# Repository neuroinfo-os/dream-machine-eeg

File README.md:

# Dream Machine
The Dream Machine, formerly known as *Traumschreiber*, is a lightweight, low-cost, mobile EEG device developed at the Neuroinforamtics group at Osnabrück University. This repository contains all affiliated projects and theses.

### This includes:
- BoardDesign: The Printed Circuit Board (PCB) design of the latest version and a collection of operation manuals of the most important hardware components
- Two App submodules, including the [standard version](https://github.com/denizmgun/EEG-DroidDesign) and an alternative version adapted for an [exemplary motor imagery task](https://github.com/denizmgun/DreamMachineThesisMod)
- The embedded system and Bluetooth Low Energy (BLE) implementation
- An implementation to perform an "Eyes Open, Eyes Closed" experiment with Labrecorder and lab streaming layer (LSL) as [submodule](https://github.com/mvidaldp/pylsl-keyboard-trigger)
- A collection of theses written with (older) versions of the Dream Machine   

*Please do not hesitate to contact us with any questions or ideas (Paria Samimi: psamimi@uni-osnabrueck.de, Laura Krieger: laura.krieger@uni-osnabrueck.de).*

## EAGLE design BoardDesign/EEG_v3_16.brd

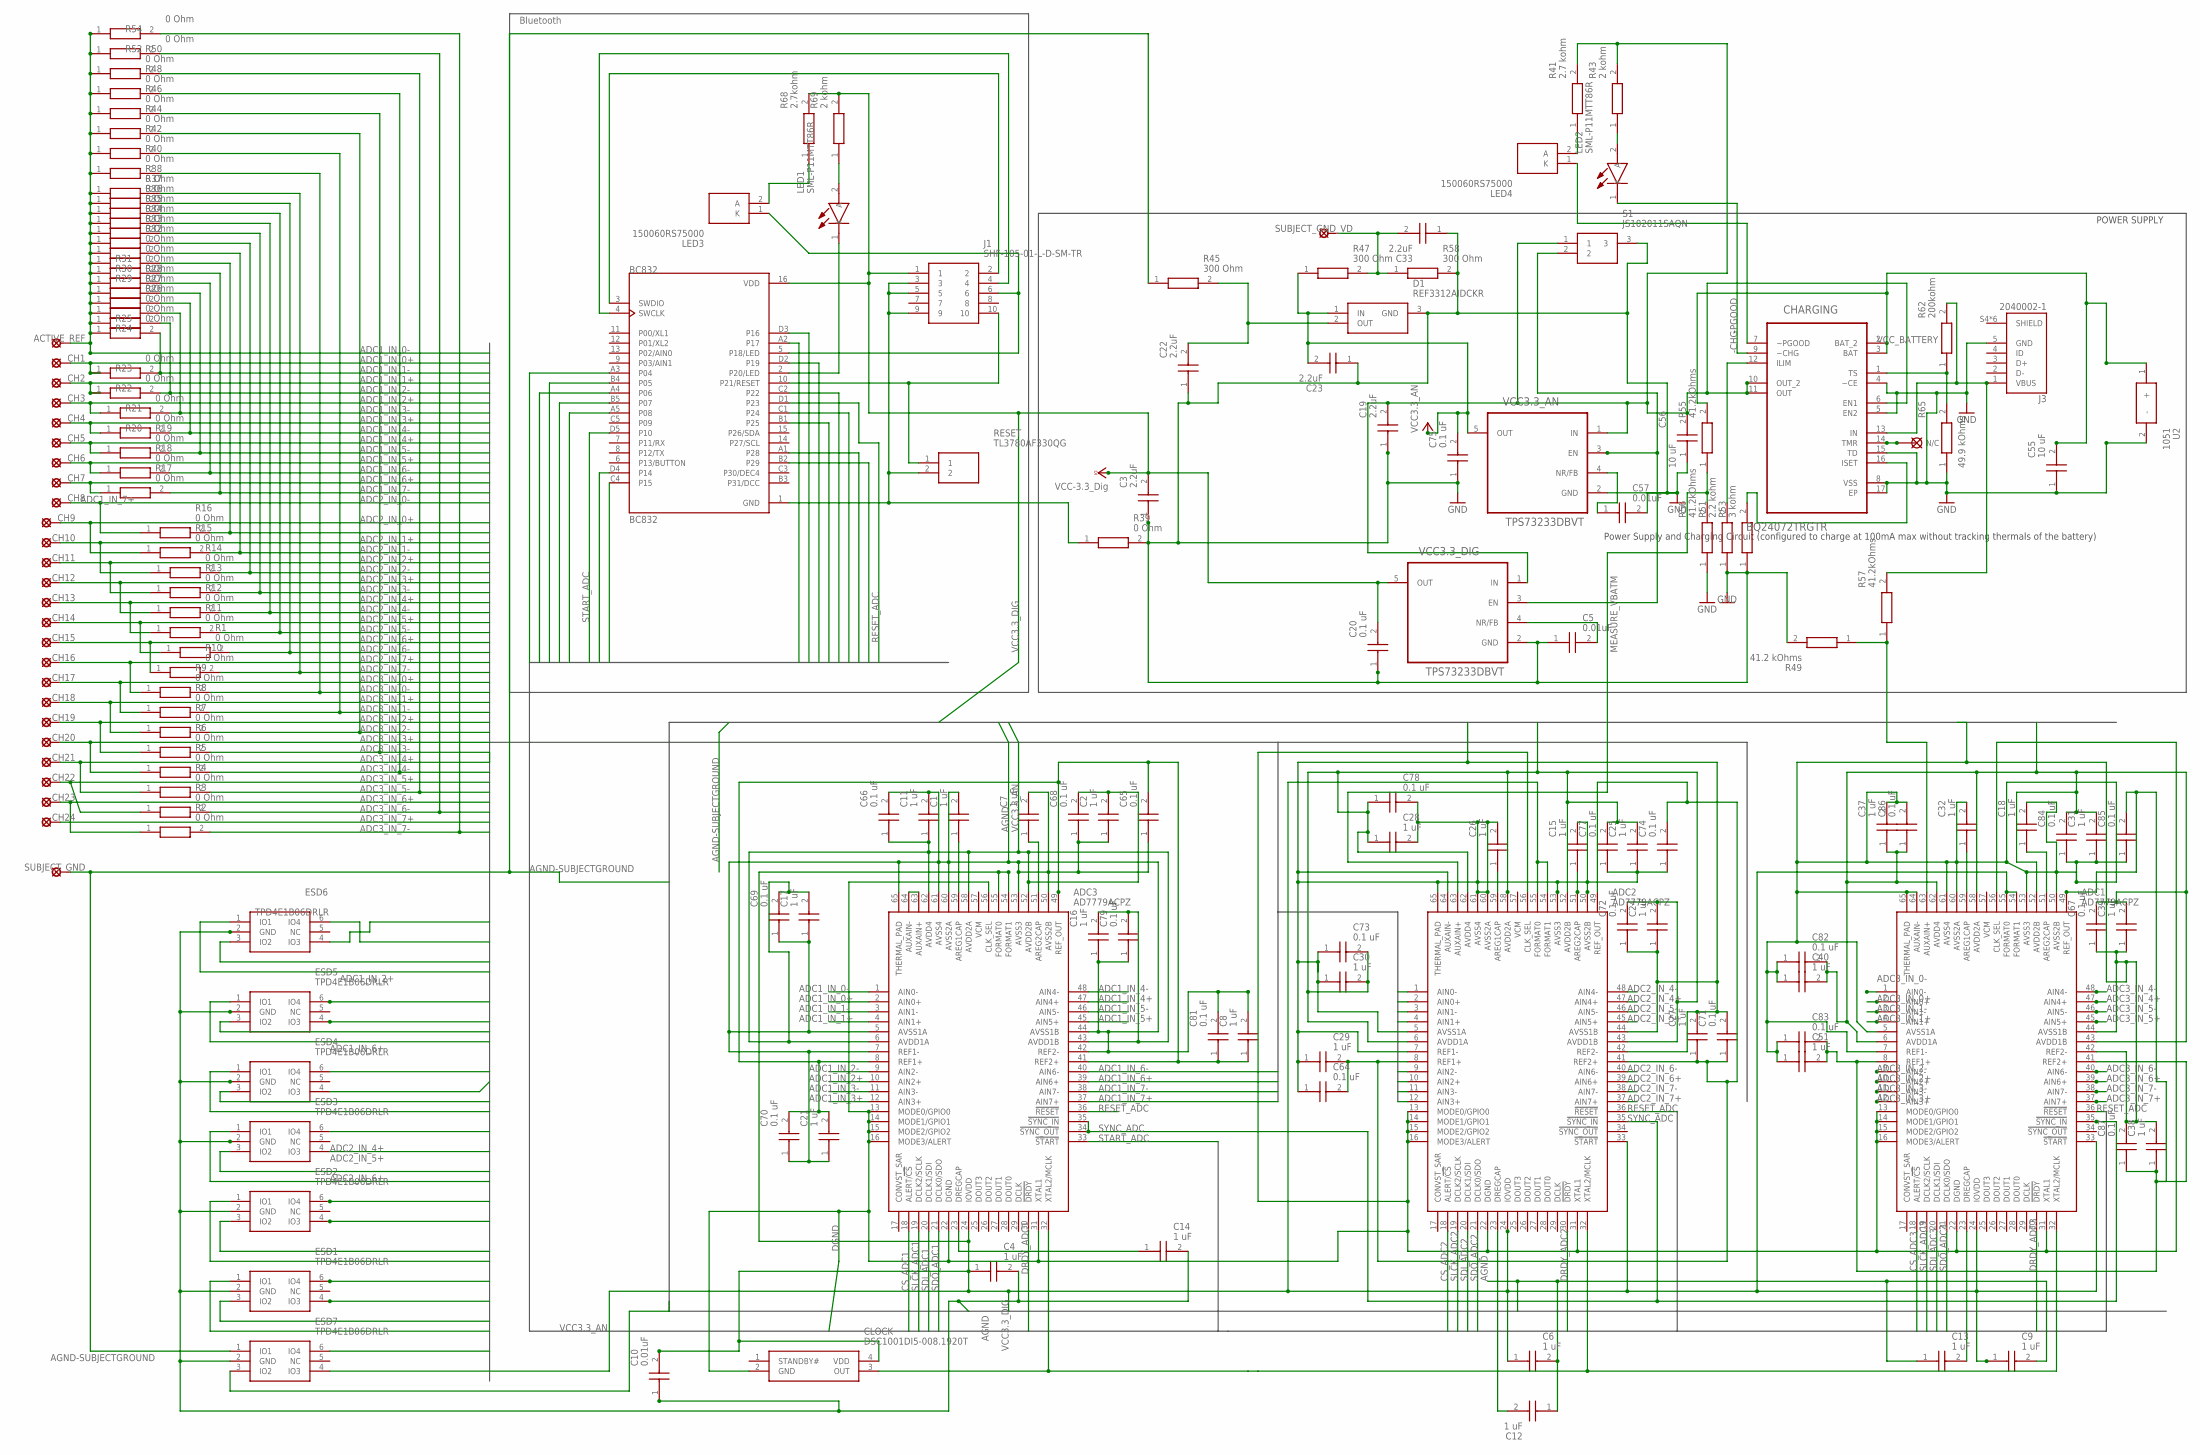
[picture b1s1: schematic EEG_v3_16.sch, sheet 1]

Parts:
ACTIVE_REF: SE11
ADC1, ADC2, ADC3: AD7779ACPZ; QFN50P900X900X80-65N
BC832: BC832; XCVR_BC832
C1, C2, C4, C6, C7, C8, C9, C11, C12, C13, C14, C15, C16, C17, C18, C21, C24, C25, C26, C27, C28, C29, C30, C31, C32, C37, C38, C39, C40, C51: 1 uF; CAPC1005X33N
C3, C19, C22, C23, C33: 2.2uF; CAPC0603X33N
C5, C10, C57: 0.01uF; CAPC0603X33N
C20, C64, C65, C66, C67, C68, C69, C70, C71, C72, C73, C74, C75, C77, C78, C79, C81, C82, C83, C84, C85, C86, C87: 0.1 uF; CAPC0603X33N
C55, C56: 10 uF; CAPC1608X100N
CH1, CH2, CH3, CH4, CH5, CH6, CH7, CH8, CH9, CH10, CH11, CH12, CH13, CH14, CH15, CH16, CH17, CH18, CH19, CH20, CH21, CH22, CH23, CH24: SE11
CHARGING: BQ24072TRGTR; QFN50P300X300X100-17N
CLOCK: DSC1001DI5-008.1920T; DSC1001DI50081920T
D1: REF3312AIDCKR; SOT65P210X110-3N
ESD1, ESD2, ESD3, ESD4, ESD5, ESD6, ESD7: TPD4E1B06DRLR; SOP50P160X60-6N
J1: SHF-105-01-L-D-SM-TR; SHF-105-01-X-D-SM-TR
J3: 2040002-1; TE_2040002-1
LED1, LED2: SML-P11MTT86R; LEDC1006X25N
LED3, LED4: 150060RS75000; LEDC1608X80N
R1, R2, R3, R4, R5, R6, R7, R8, R9, R10, R11, R12, R13, R14, R15, R16, R17, R18, R19, R20, R21, R22, R23, R24, R25, R26, R27, R28, R29, R30, R31, R32, R33, R34, R35, R36, R37, R38, R39, R40, R42, R44, R46, R48, R50, R52, R54: 0 Ohm; RESC1608X55N
R41: 2.7 kohm; RESC0603X26N
R43, R69: 2 kohm; RESC0603X26N
R45, R47, R58: 300 Ohm; RESC0603X26N
R49: 41.2 kOhms; RESC0603X28N
R51: 2.2 kohm; RESC0603X28N
R53: 3 kohm; RESC0603X26N
R55, R56, R57: 41.2kOhms; RESC0603X28N
R62: 200kohm; RESC0603X28N
R65: 49.9 kOhms; RESC0603X28N
R68: 2.7kohm; RESC0603X26N
RESET: TL3780AF330QG
S1: JS102011SAQN
SUBJECT_GND: SE11
SUBJECT_GND_VD: SE11
U2: 1051
VCC3.3_AN, VCC3.3_DIG: TPS73233DBVT; SOT95P280X145-5N

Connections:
-CHG: CHARGING.9 (~CHG), LED2.1 (K)
-PGOOD: CHARGING.7 (~PGOOD), LED4.1 (K)
ADC1_IN_0+: ADC3.2 (AIN0+), CH1.MP, ESD6.4 (IO3), R23.1
ADC1_IN_0-: ACTIVE_REF.MP, ADC3.1 (AIN0-), ESD6.6 (IO4), R24.1, R25.1, R26.1, R27.1, R28.1, R29.1, R30.1, R31.1, R32.1, R33.1, R34.1, R35.1, R36.1, R37.1, R38.1, R40.1, R42.1, R44.1, R46.1, R48.1, R50.1, R52.1, R54.1
ADC1_IN_1+: ADC3.4 (AIN1+), CH2.MP, ESD6.3 (IO2), R22.1
ADC1_IN_1-: ADC3.3 (AIN1-), R23.2, R24.2
ADC1_IN_2+: ADC3.10 (AIN2+), CH3.MP, ESD6.1 (IO1), R21.1
ADC1_IN_2-: ADC3.9 (AIN2-), R22.2, R25.2
ADC1_IN_3+: ADC3.12 (AIN3+), CH4.MP, ESD5.6 (IO4), R20.1
ADC1_IN_3-: ADC3.11 (AIN3-), R21.2, R26.2
ADC1_IN_4+: ADC3.47 (AIN4+), CH5.MP, ESD5.4 (IO3), R19.1
ADC1_IN_4-: ADC3.48 (AIN4-), R20.2, R27.2
ADC1_IN_5+: ADC3.45 (AIN5+), CH6.MP, ESD5.3 (IO2), R18.1
ADC1_IN_5-: ADC3.46 (AIN5-), R19.2, R28.2
ADC1_IN_6+: ADC3.39 (AIN6+), CH7.MP, ESD5.1 (IO1), R17.1
ADC1_IN_6-: ADC3.40 (AIN6-), R18.2, R29.2
ADC1_IN_7+: ADC3.37 (AIN7+), CH8.MP, ESD4.6 (IO4), R16.1
ADC1_IN_7-: ADC3.38 (AIN7-), R17.2, R30.2
ADC2_IN_0+: ADC2.2 (AIN0+), CH9.MP, ESD4.4 (IO3), R15.1
ADC2_IN_0-: ADC2.1 (AIN0-), R16.2, R31.2
ADC2_IN_1+: ADC2.4 (AIN1+), CH10.MP, ESD4.3 (IO2), R14.1
ADC2_IN_1-: ADC2.3 (AIN1-), R15.2, R32.2
ADC2_IN_2+: ADC2.10 (AIN2+), CH11.MP, ESD4.1 (IO1), R13.1
ADC2_IN_2-: ADC2.9 (AIN2-), R14.2, R33.2
ADC2_IN_3+: ADC2.12 (AIN3+), CH12.MP, ESD3.6 (IO4), R12.1
ADC2_IN_3-: ADC2.11 (AIN3-), R13.2, R34.2
ADC2_IN_4+: ADC2.47 (AIN4+), CH13.MP, ESD3.4 (IO3), R11.1
ADC2_IN_4-: ADC2.48 (AIN4-), R12.2, R35.2
ADC2_IN_5+: ADC2.45 (AIN5+), CH14.MP, ESD3.3 (IO2), R1.1
ADC2_IN_5-: ADC2.46 (AIN5-), R11.2, R36.2
ADC2_IN_6+: ADC2.39 (AIN6+), CH15.MP, ESD3.1 (IO1), R10.1
ADC2_IN_6-: ADC2.40 (AIN6-), R1.2, R37.2
ADC2_IN_7+: ADC2.37 (AIN7+), CH16.MP, ESD2.6 (IO4), R9.1
ADC2_IN_7-: ADC2.38 (AIN7-), R10.2, R38.2
ADC3_IN_0+: ADC1.2 (AIN0+), CH17.MP, ESD2.4 (IO3), R8.1
ADC3_IN_0-: ADC1.1 (AIN0-), R9.2, R40.2
ADC3_IN_1+: ADC1.4 (AIN1+), CH18.MP, ESD2.3 (IO2), R7.1
ADC3_IN_1-: ADC1.3 (AIN1-), R8.2, R42.2
ADC3_IN_2+: ADC1.10 (AIN2+), CH19.MP, ESD2.1 (IO1), R6.1
ADC3_IN_2-: ADC1.9 (AIN2-), R7.2, R44.2
ADC3_IN_3+: ADC1.12 (AIN3+), CH20.MP, ESD1.6 (IO4), R5.1
ADC3_IN_3-: ADC1.11 (AIN3-), R6.2, R46.2
ADC3_IN_4+: ADC1.47 (AIN4+), CH21.MP, ESD1.4 (IO3), R4.1
ADC3_IN_4-: ADC1.48 (AIN4-), R5.2, R48.2
ADC3_IN_5+: ADC1.45 (AIN5+), CH22.MP, ESD1.3 (IO2), R3.1
ADC3_IN_5-: ADC1.46 (AIN5-), R4.2, R50.2
ADC3_IN_6+: ADC1.39 (AIN6+), CH23.MP, ESD1.1 (IO1), R2.1
ADC3_IN_6-: ADC1.40 (AIN6-), R3.2, R52.2
ADC3_IN_7+: ADC1.37 (AIN7+), CH24.MP, ESD7.6 (IO4)
ADC3_IN_7-: ADC1.38 (AIN7-), R2.2, R54.2
AGND: ADC1.5 (AVSS1A), ADC1.7 (REF1-), ADC1.42 (REF2-), ADC1.44 (AVSS1B), ADC1.50 (AVSS2B), ADC1.53 (AVSS3), ADC1.60 (AVSS2A), ADC1.61 (AVSS4), ADC1.64 (AUXAIN-), ADC1.65 (THERMAL_PAD), ADC2.5 (AVSS1A), ADC2.7 (REF1-), ADC2.42 (REF2-), ADC2.44 (AVSS1B), ADC2.50 (AVSS2B), ADC2.53 (AVSS3), ADC2.60 (AVSS2A), ADC2.61 (AVSS4), ADC2.64 (AUXAIN-), ADC2.65 (THERMAL_PAD), ADC3.5 (AVSS1A), ADC3.7 (REF1-), ADC3.42 (REF2-), ADC3.44 (AVSS1B), ADC3.50 (AVSS2B), ADC3.53 (AVSS3), ADC3.60 (AVSS2A), ADC3.61 (AVSS4), ADC3.65 (THERMAL_PAD), C1.2, C2.1, C3.1, C4.2, C5.1, C6.2, C7.2, C8.2, C9.2, C10.1, C11.2, C12.1, C13.1, C14.2, C15.2, C16.1, C17.1, C18.2, C19.1, C20.1, C21.1, C22.1, C23.1, C24.1, C25.1, C26.2, C27.2, C28.2, C29.1, C30.1, C31.1, C32.2, C33.1, C37.2, C38.2, C39.1, C40.1, C51.1, C55.1, C56.1, C57.2, C64.1, C65.1, C66.2, C67.1, C68.1, C69.1, C70.1, C71.2, C72.1, C73.1, C74.1, C75.1, C77.1, C78.2, C79.1, C81.2, C82.1, C83.1, C84.1, C85.1, C86.2, C87.2, CHARGING.4 (~CE), CHARGING.5 (EN2), CHARGING.8 (VSS), CHARGING.15 (TD), CHARGING.17 (EP), D1.3 (GND), ESD1.2 (GND), ESD2.2 (GND), ESD3.2 (GND), ESD4.2 (GND), ESD5.2 (GND), ESD6.2 (GND), ESD7.2 (GND), J3.5 (GND), R39.2, R49.2, R51.1, R53.1, R56.1, R58.2, R65.1, S1.3, U2.2 (-), VCC3.3_AN.2 (GND), VCC3.3_DIG.2 (GND)
AGND-SUBJECTGROUND: ESD7.1 (IO1), R45.1, SUBJECT_GND.MP
CS_ADC1: ADC3.18 (ALERT/!CS), BC832.A4 (P06)
CS_ADC2: ADC2.18 (ALERT/!CS), BC832.A5 (P08)
CS_ADC3: ADC1.18 (ALERT/!CS), BC832.C1 (P24)
DGND: ADC1.13 (MODE0/GPIO0), ADC1.14 (MODE1/GPIO1), ADC1.15 (MODE2/GPIO2), ADC1.16 (MODE3/ALERT), ADC1.22 (DGND), ADC1.31 (XTAL1), ADC1.56 (CLK_SEL), ADC2.13 (MODE0/GPIO0), ADC2.14 (MODE1/GPIO1), ADC2.15 (MODE2/GPIO2), ADC2.16 (MODE3/ALERT), ADC2.22 (DGND), ADC2.31 (XTAL1), ADC2.56 (CLK_SEL), ADC3.13 (MODE0/GPIO0), ADC3.14 (MODE1/GPIO1), ADC3.15 (MODE2/GPIO2), ADC3.16 (MODE3/ALERT), ADC3.22 (DGND), ADC3.31 (XTAL1), ADC3.56 (CLK_SEL), BC832.1 (GND), CLOCK.2 (GND), J1.3, J1.5, J1.9, R39.1, RESET.2
DRDY_ADC1: ADC3.30 (!DRDY), BC832.A2 (P17)
DRDY_ADC2: ADC2.30 (!DRDY), BC832.D4 (P14)
DRDY_ADC3: ADC1.30 (!DRDY), BC832.B1 (P25)
MEASURE_VBATM: ADC2.63 (AUXAIN+), R55.1, R56.2
MEASURE_VUSB: ADC1.63 (AUXAIN+), R49.1, R57.1
unnamed: ADC3.59 (AREG1CAP), C1.1
unnamed: ADC2.23 (DREGCAP), C12.2
unnamed: C22.2, D1.2 (OUT), R45.2
unnamed: C5.2, VCC3.3_DIG.4 (NR/FB)
unnamed: BC832.2 (P20/LED), LED1.1 (K)
unnamed: ADC3.63 (AUXAIN+), ADC3.64 (AUXAIN-)
unnamed: ADC3.51 (AREG2CAP), C7.1
unnamed: LED3.2 (A), R68.1
unnamed: LED1.2 (A), R69.1
unnamed: LED4.2 (A), R41.1
unnamed: ADC2.51 (AREG2CAP), C15.1
unnamed: ADC3.23 (DREGCAP), C14.1
unnamed: ADC1.23 (DREGCAP), C13.2
unnamed: LED2.2 (A), R43.1
unnamed: C57.1, VCC3.3_AN.4 (NR/FB)
unnamed: ADC1.59 (AREG1CAP), C32.1
unnamed: ADC2.59 (AREG1CAP), C26.1
unnamed: ADC1.51 (AREG2CAP), C18.1
unnamed: CHARGING.1 (TS), R62.1, R65.2
unnamed: CHARGING.16 (ISET), R53.2
unnamed: CHARGING.12 (ILIM), R51.2
P18/LED: BC832.5 (P18/LED), J1.6, LED3.1 (K)
POWERUP: S1.2, VCC3.3_AN.3 (EN), VCC3.3_DIG.3 (EN)
REF_ADC1: ADC3.8 (REF1+), ADC3.41 (REF2+), ADC3.49 (REF_OUT), C8.1, C21.2, C65.2, C70.2, C81.1
REF_ADC2: ADC2.8 (REF1+), ADC2.41 (REF2+), ADC2.49 (REF_OUT), C27.1, C29.2, C64.2, C71.1, C74.2
REF_ADC3: ADC1.8 (REF1+), ADC1.41 (REF2+), ADC1.49 (REF_OUT), C38.1, C51.2, C83.2, C85.2, C87.1
RESET: BC832.10 (P21/RESET), J1.10, RESET.1
RESET_ADC: ADC1.36 (!RESET), ADC2.36 (!RESET), ADC3.36 (!RESET), BC832.D1 (P23)
SDCLK: BC832.4 (SWCLK), J1.4
SDIO: BC832.3 (SWDIO), J1.2
SDI_ADC1: ADC3.20 (DCLK1/SDI), BC832.C4 (P15)
SDI_ADC2: ADC2.20 (DCLK1/SDI), BC832.B5 (P07)
SDI_ADC3: ADC1.20 (DCLK1/SDI), BC832.A1 (P28)
SDO_ADC1: ADC3.21 (DCLK0/SDO), BC832.D3 (P16)
SDO_ADC2: ADC2.21 (DCLK0/SDO), BC832.B4 (P05)
SDO_ADC3: ADC1.21 (DCLK0/SDO), BC832.B2 (P29)
SHIELD: J3.S4 (SHIELD), J3.S5 (SHIELD), J3.SH1 (SHIELD), J3.SH2 (SHIELD), J3.SH3 (SHIELD), J3.SH4 (SHIELD)
SLCK_ADC1: ADC3.19 (DCLK2/SCLK), BC832.A3 (P04)
SLCK_ADC2: ADC2.19 (DCLK2/SCLK), BC832.D2 (P19)
SLCK_ADC3: ADC1.19 (DCLK2/SCLK), BC832.C2 (P22)
START_ADC: ADC3.33 (!START), BC832.D5 (P10)
SYNC_ADC: ADC1.35 (!SYNC_IN), ADC2.35 (!SYNC_IN), ADC3.34 (!SYNC_OUT), ADC3.35 (!SYNC_IN)
USB_5VOLT+: CHARGING.13 (IN), J3.1 (VBUS), R57.2, R62.2
VCC3.3_AN: ADC1.6 (AVDD1A), ADC1.43 (AVDD1B), ADC1.52 (AVDD2B), ADC1.58 (AVDD2A), ADC1.62 (AVDD4), ADC2.6 (AVDD1A), ADC2.43 (AVDD1B), ADC2.52 (AVDD2B), ADC2.58 (AVDD2A), ADC2.62 (AVDD4), ADC3.6 (AVDD1A), ADC3.43 (AVDD1B), ADC3.52 (AVDD2B), ADC3.58 (AVDD2A), ADC3.62 (AVDD4), C2.2, C11.1, C16.2, C17.2, C23.2, C24.2, C25.2, C28.1, C30.2, C31.2, C37.1, C39.2, C40.2, C66.1, C67.2, C68.2, C69.2, C72.2, C73.2, C75.2, C77.2, C78.1, C79.2, C82.2, C84.2, C86.1, D1.1 (IN), ESD7.3 (IO2), R47.1, VCC3.3_AN.5 (OUT)
VCC3.3_DIG: ADC1.24 (IOVDD), ADC1.33 (!START), ADC1.54 (FORMAT1), ADC1.55 (FORMAT0), ADC2.24 (IOVDD), ADC2.33 (!START), ADC2.54 (FORMAT1), ADC2.55 (FORMAT0), ADC3.24 (IOVDD), ADC3.54 (FORMAT1), ADC3.55 (FORMAT0), BC832.16 (VDD), C3.2, C4.1, C6.1, C9.1, C10.2, C20.2, CLOCK.4 (VDD), ESD7.4 (IO3), J1.1, R68.2, R69.2, VCC3.3_DIG.5 (OUT)
VCC_BATTERY: C55.2, CHARGING.2 (BAT_2), CHARGING.3 (BAT), R55.2, U2.1 (+)
VIRTUAL_GND_PASSIVE: C33.2, R47.2, R58.1, SUBJECT_GND_VD.MP
V_OUT_CHARGER: C19.2, C56.2, CHARGING.6 (EN1), CHARGING.10 (OUT_2), CHARGING.11 (OUT), R41.2, R43.2, S1.1, VCC3.3_AN.1 (IN), VCC3.3_DIG.1 (IN)
XTAL_OUT: ADC1.32 (XTAL2/MCLK), ADC2.32 (XTAL2/MCLK), ADC3.32 (XTAL2/MCLK), CLOCK.3 (OUT)

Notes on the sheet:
Power Supply and Charging Circuit (configured to charge at 100mA max without tracking thermals of the battery)
POWER SUPPLY
Bluetooth

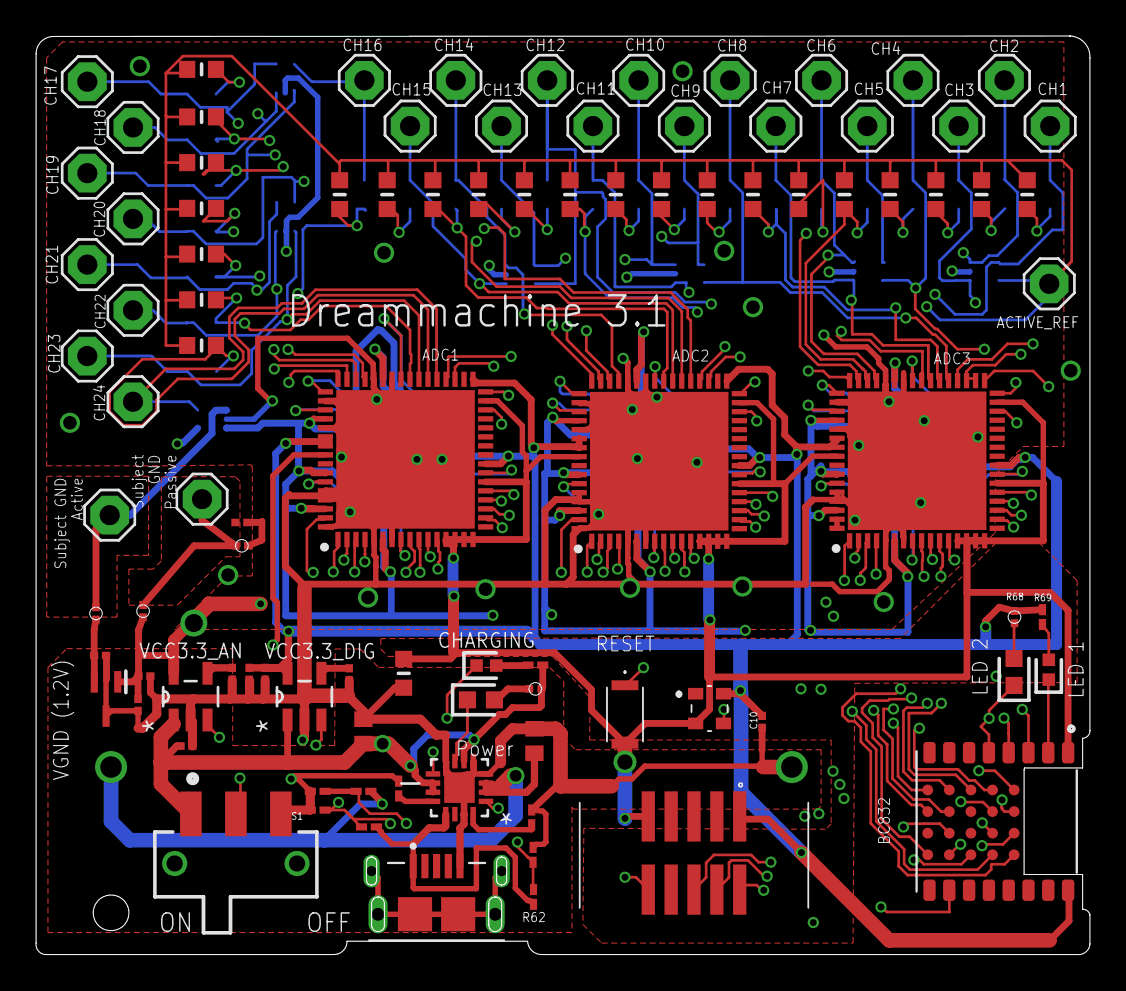
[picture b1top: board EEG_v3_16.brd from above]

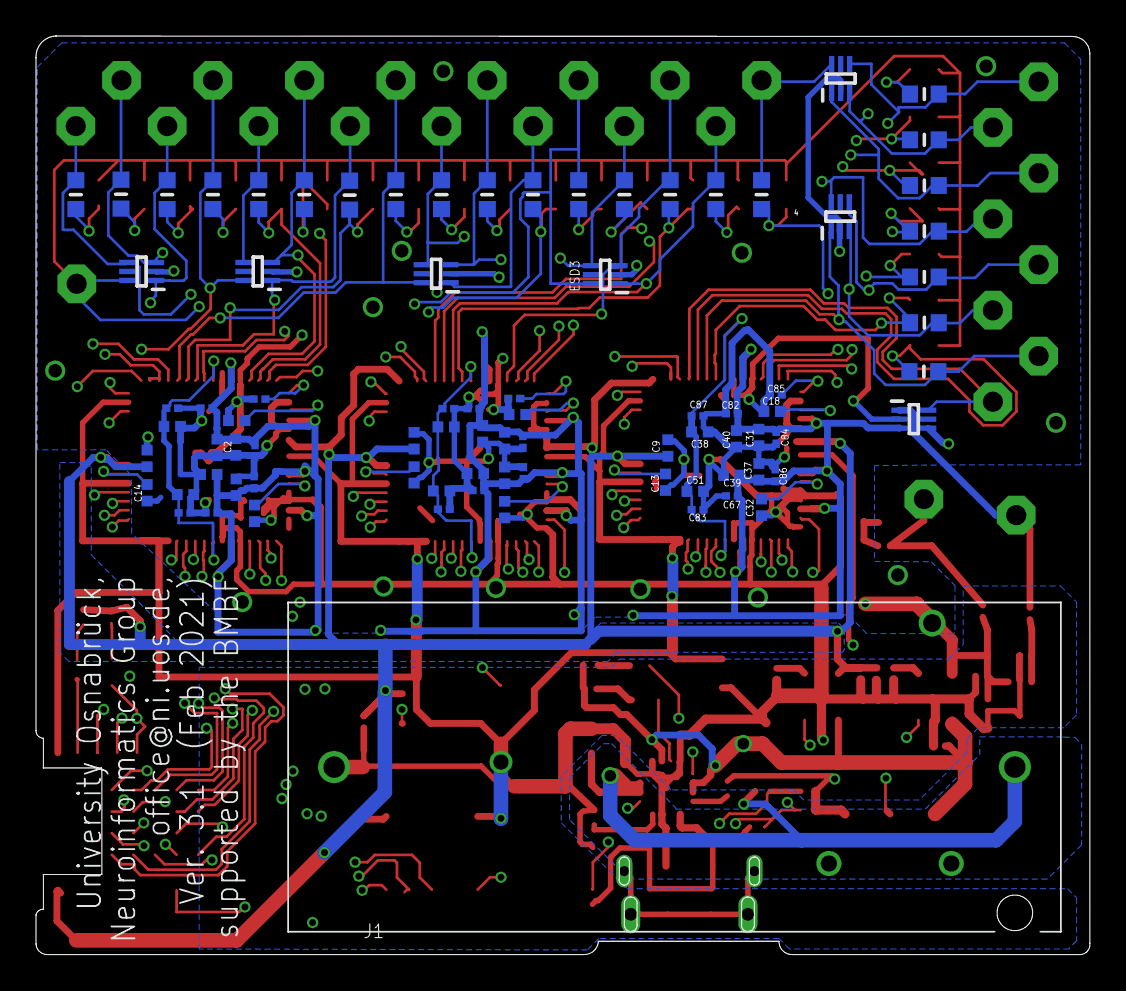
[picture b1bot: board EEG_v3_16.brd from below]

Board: 4 copper layers, 58.6 x 51.0 mm, 177 parts (82 on the bottom side), 110 nets.

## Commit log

2022-06-01 Add App submodules
2022-06-01 Add lsl submodules
2022-06-03 Create PCB Board Design
2022-06-03 PCB Board Design
2022-06-03 Create Board Design
